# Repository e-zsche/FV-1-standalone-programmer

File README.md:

# Micropython FV-1 flasher

Small project for flashing 24LC32A EEPROMs using any microcontroller which has enough flash and
is able to run Micropython. Just because, a raspberry pico is used.

# Code

Huge thanks to ndf-zz for writing the asfv1 assembler. Without your work this would not be possible.
<https://github.com/ndf-zz/asfv1/>

As shlex is not in the standard Micropython library a copy of the source code is obtained and used
for running the asfv1 assembler. To get it running on the MCU one line is removed. So far this does
not seem to have an impact when running the code.

FV-1 programs are stored and read with a micro SD-card. All programs have to be in the root directory
and must have the `.spn` file extension to be found.

# Hardware

Everything is run by a Raspberry Pi Pico MCU.

User interface consists of:
- Display
- SD card slot
- EEPROM sockets
- Buttons

## Display

TFT display because it is cheaper than an OLED.
Has the SD card slot integrated.

## SD Card

Connected via SPI. Slot is Integrated into display module.

## EEPROM sockets

There are two positions on the PCB. One is for THT chips, the other for SMD chips.
SMD socket is the <a href="https://www.adafruit.com/product/4726">SOIC-8 socket from adafruit</a>

Make sure to insert the EEPROM with the correct orientation!!

## Buttons

In total there are five buttons arranged as a sort of D-Pad and a shift button.

Controls:
- up and down for scrolling through file list (faster scrolling when holding shift button)
- left and right for selecting program slot of selected file
- middle button
  * start programming (when not selecting slot)
  * selecting slot

# Obtain SPN files

Writing programs yourself for the FV-1 is good way to get some programs. Info on the assembly
language is a little harder to find than info on the FV-1 hardware. However there are some
sources inside a forum dating back to 2019:

- <a href="https://xenvn.com/threads/spin-fv-1-audio-effects.125">Spin FV-1 Audio Effects</a>
- <a href="https://xenvn.com/threads/spin-fv-1-instructions-and-syntax.122/">Spin FV-1 Instructions and Syntax</a>
- <a href="https://xenvn.com/threads/basics-of-the-lfos-in-the-spin-fv-1.123/">Basics of the LFOs in the Spin FV-1</a>

This is about all the info I could find on the assembly instructions itself...

Another wonderful source of programs is mstratman's collection of programs:

<https://mstratman.github.io/fv1-programs/>

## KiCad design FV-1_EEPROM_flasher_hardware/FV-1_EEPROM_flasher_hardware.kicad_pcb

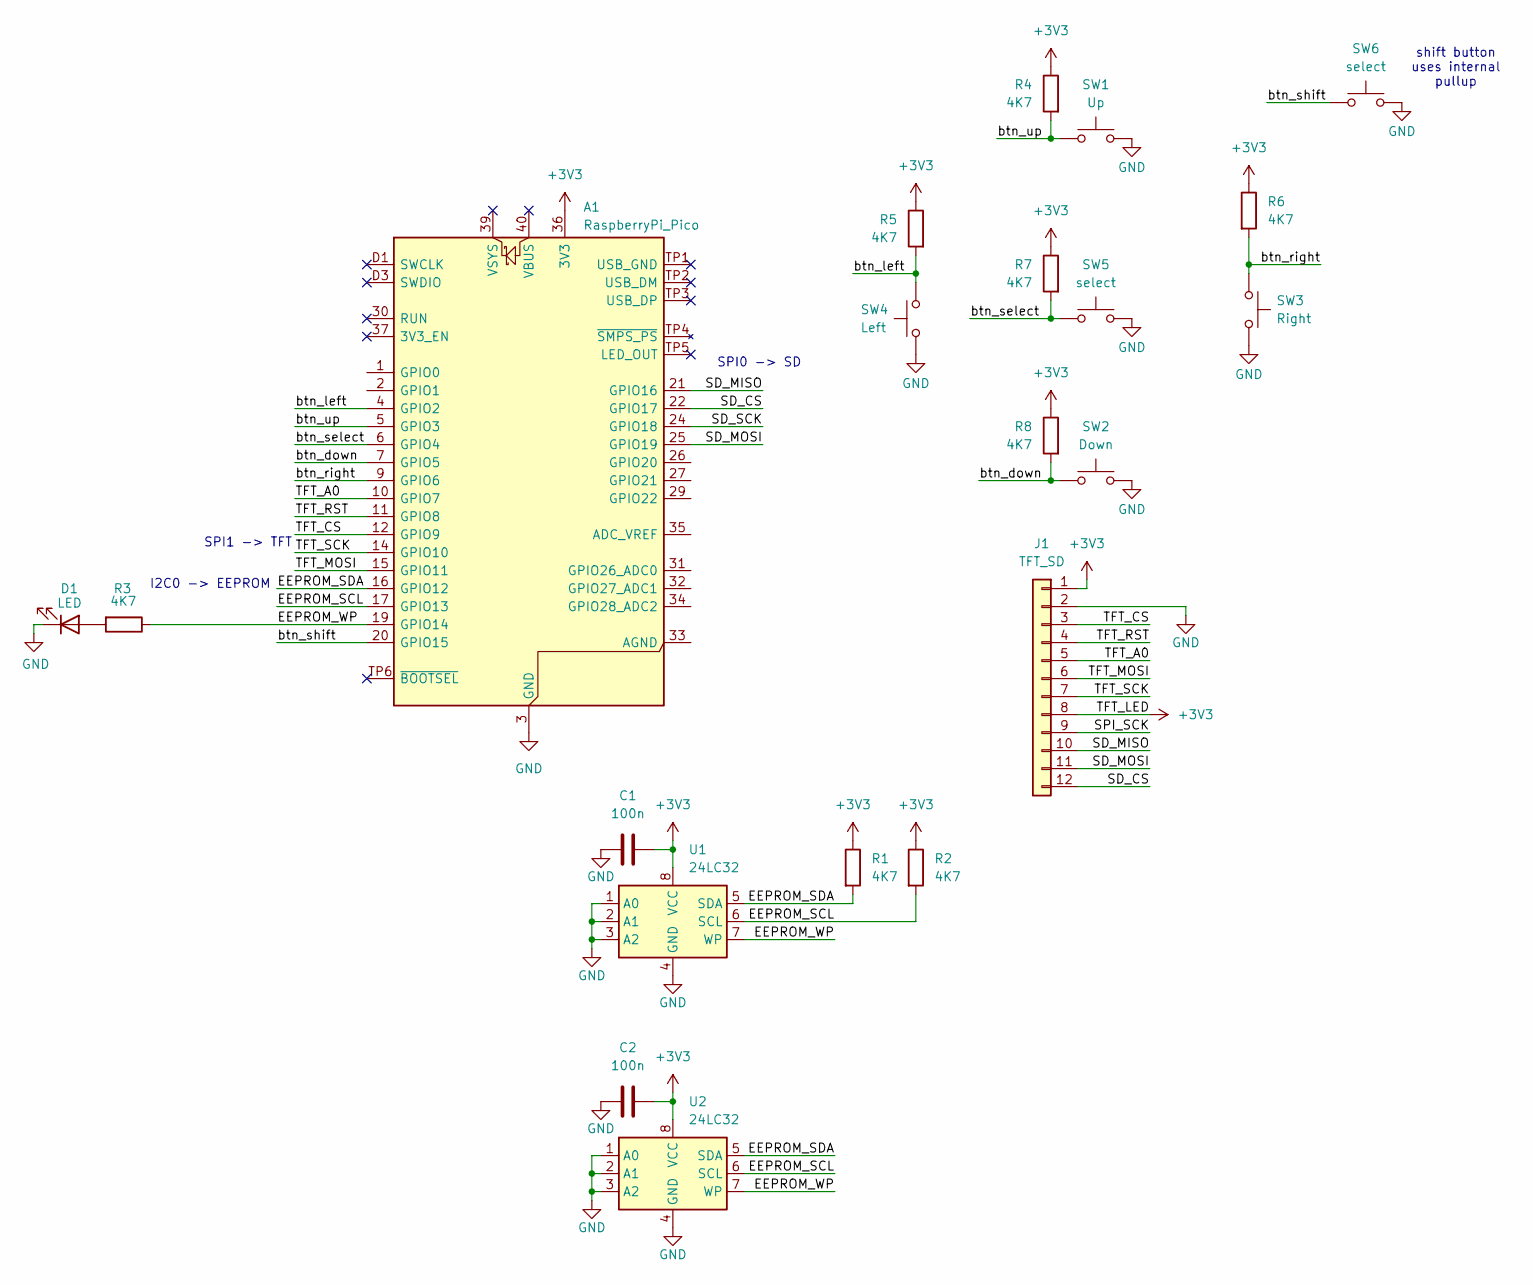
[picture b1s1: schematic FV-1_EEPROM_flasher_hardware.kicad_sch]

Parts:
A1: RaspberryPi_Pico; RaspberryPi_Pico_SMD
C1, C2: 100n; C_0805
D1: LED; LED_0805_2012Metric_Pad1.15x1.40mm_HandSolder
J1: TFT_SD; TFT_with_SD
R1, R2, R3, R4, R5, R6, R7, R8: 4K7; R_0805_2012Metric_Pad1.20x1.40mm_HandSolder
SW1: Up; SW_PUSH_6mm_H5mm
SW2: Down; SW_PUSH_6mm_H5mm
SW3: Right; SW_PUSH_6mm_H5mm
SW4: Left; SW_PUSH_6mm_H5mm
SW5, SW6: select; SW_PUSH_6mm_H5mm
U1: 24LC32; DIP-8_W7.62mm_Socket_LongPads
U2: 24LC32; SOIC-8_5.3x5.3mm_P1.27mm

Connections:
+3V3: A1.36 (3V3), C1.2, C2.2, J1.1, J1.8, R1.1, R2.1, R4.1, R5.1, R6.1, R7.1, R8.1, U1.8 (VCC), U2.8 (VCC)
/EEPROM_SCL: A1.17 (GPIO13), R2.2, U1.6 (SCL), U2.6 (SCL)
/EEPROM_SDA: A1.16 (GPIO12), R1.2, U1.5 (SDA), U2.5 (SDA)
/EEPROM_WP: A1.19 (GPIO14), R3.1, U1.7 (WP), U2.7 (WP)
/SD_CS: A1.22 (GPIO17), J1.12
/SD_MISO: A1.21 (GPIO16), J1.10
/SD_MOSI: A1.25 (GPIO19), J1.11
/SD_SCK: A1.24 (GPIO18)
/SPI_SCK: J1.9
/TFT_A0: A1.10 (GPIO7), J1.5
/TFT_CS: A1.12 (GPIO9), J1.3
/TFT_MOSI: A1.15 (GPIO11), J1.6
/TFT_RST: A1.11 (GPIO8), J1.4
/TFT_SCK: A1.14 (GPIO10), J1.7
/btn_down: A1.7 (GPIO5), R8.2, SW2.1
/btn_left: A1.4 (GPIO2), R5.2, SW4.2
/btn_right: A1.9 (GPIO6), R6.2, SW3.1
/btn_select: A1.6 (GPIO4), R7.2, SW5.1
/btn_shift: A1.20 (GPIO15), SW6.1
/btn_up: A1.5 (GPIO3), R4.2, SW1.1
GND: A1.3 (GND), A1.8 (GND), A1.13 (GND), A1.18 (GND), A1.23 (GND), A1.28 (GND), A1.38 (GND), A1.D2 (GND), C1.1, C2.1, D1.1 (K), J1.2, SW1.2, SW2.2, SW3.2, SW4.1, SW5.2, SW6.2, U1.1 (A0), U1.2 (A1), U1.3 (A2), U1.4 (GND), U2.1 (A0), U2.2 (A1), U2.3 (A2), U2.4 (GND)
unnamed: D1.2 (A), R3.2

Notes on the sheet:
I2C0 -> EEPROM
SPI1 -> TFT
SPI0 -> SD
shift button uses internal pullup

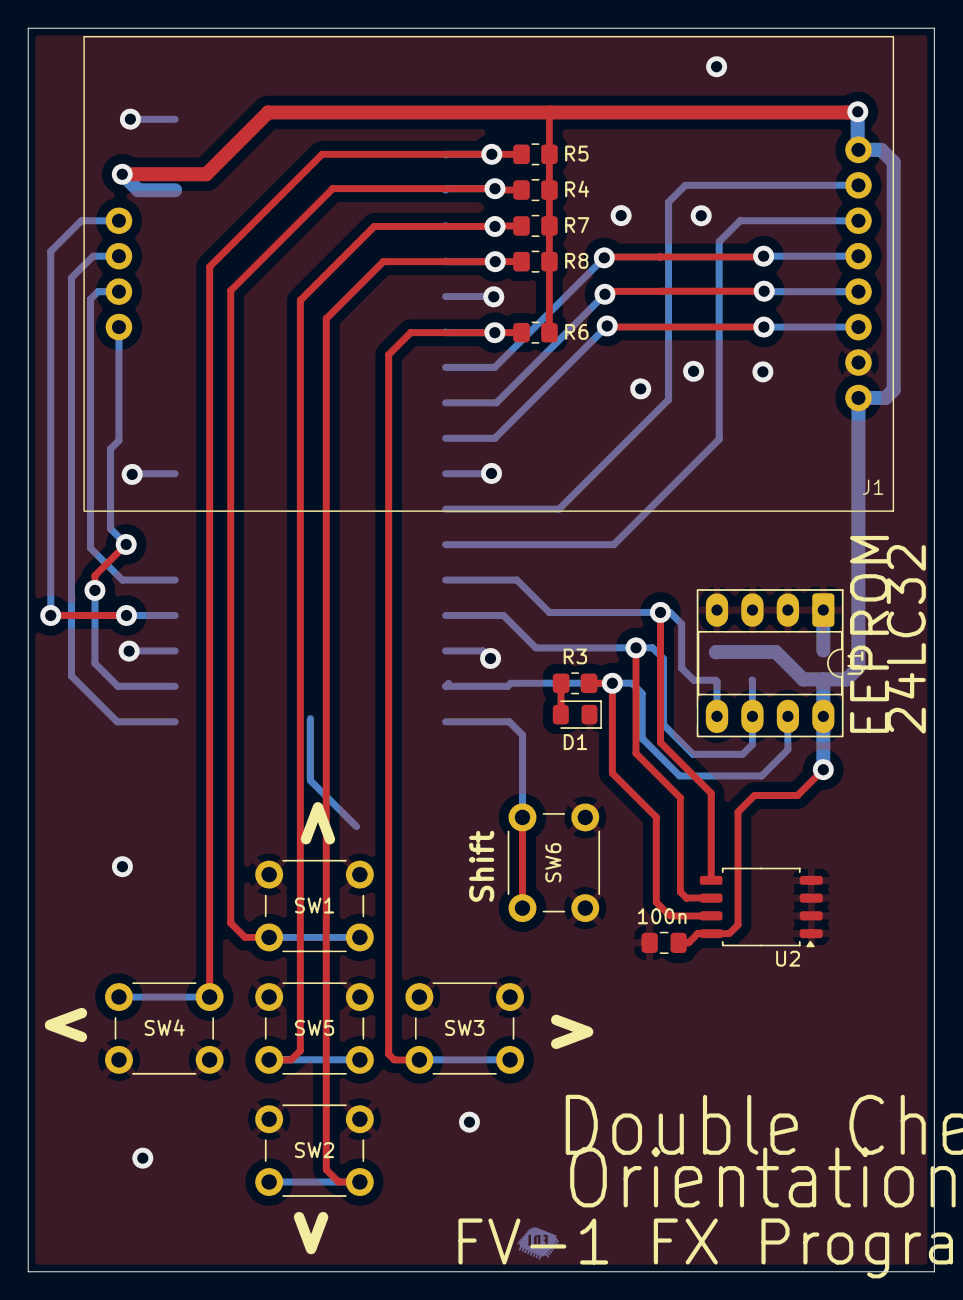
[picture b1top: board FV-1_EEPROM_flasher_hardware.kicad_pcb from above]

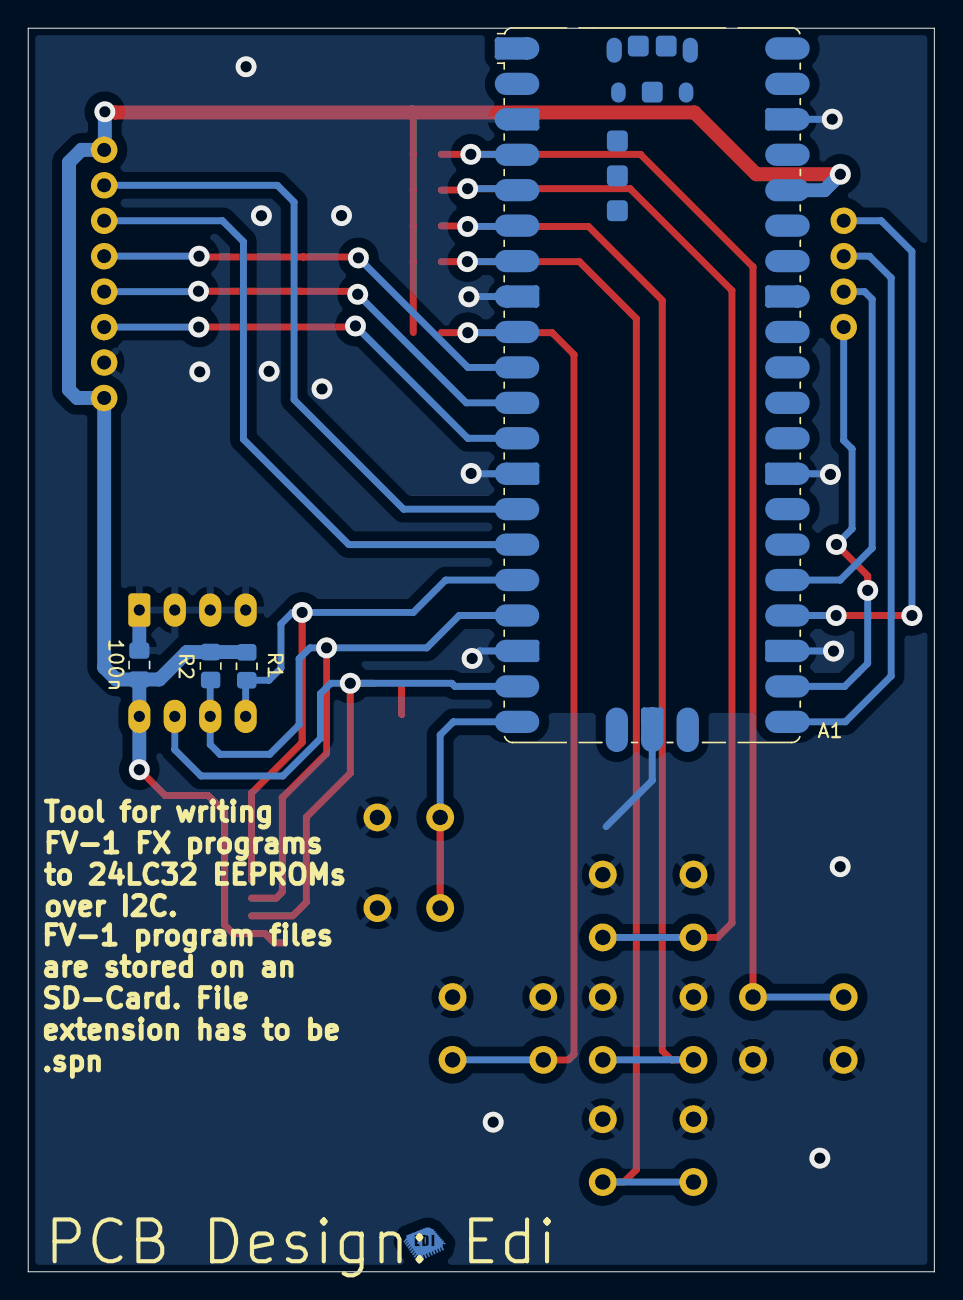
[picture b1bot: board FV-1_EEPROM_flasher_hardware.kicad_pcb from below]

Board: 2 copper layers, 64.9 x 89.1 mm, 22 parts (5 on the bottom side), 20 nets.

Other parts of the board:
Ref**: Val**; PCB_EDI_logo

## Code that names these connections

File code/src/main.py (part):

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TFT_WIDTH  = 160 # px
TFT_HEIGHT = 128 # px

btn_up      = Pin(3, Pin.IN, Pin.PULL_UP)
btn_down    = Pin(5, Pin.IN, Pin.PULL_UP)
btn_left    = Pin(2, Pin.IN, Pin.PULL_UP)
btn_right   = Pin(6, Pin.IN, Pin.PULL_UP)
btn_select  = Pin(4, Pin.IN, Pin.PULL_UP)
btn_shift   = Pin(15, Pin.IN, Pin.PULL_UP)

# TFT init
WHITE = const(0XFFFFFF)
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
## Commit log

2025-03-18 added README.md
2025-03-18 added kicad hardware folder
2025-03-18 added micropython source code
2025-03-18 added uf2 binary for rpi pico
2025-03-18 info on spn files
2025-03-18 clean up README on spn files
2025-03-18 added pics
2025-03-18 resize img
2025-03-18 removed unused SD card symbols
2025-03-18 rewrote i2c_util.py to eeprom_util.py for easier usage
2025-03-18 error on tft when file is too big for RAM
2025-03-18 bugfix: free RAM after assembling and writing program
2025-03-18 replaced status led with shift button, led connected to EEPROM write protect pin
2025-03-18 use shift button for faster scrolling
2025-03-18 briefly explain controls
2025-03-18 binary with shift button
2025-03-21 BUGFIX: fast scrolling was broken
2025-03-21 fixed missing screen update when rolling over file list
2025-03-22 fixed urls to external websites
2025-03-29 removed unnecessary libs
2025-03-29 fixed scrolling, added SD card error messages
2025-03-29 flipped EEPROM socket by 90°; PCB ready for production
2025-03-29 binary for rpi pico up to date
2025-08-02 BUGFIX: fixed wrong array indexing in write_eeprom function
